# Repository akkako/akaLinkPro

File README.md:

# akaLinkPro

akaLinkPro 是一个基于 HPM5300 的高性能 CMSIS-DAP 调试器。

- 主固件：`firmware/application_5301`
- DFU/MSC Bootloader：`firmware/bootloader_dfu`
- 配置上位机（WebHID）：`docs/index.html`

构建 / 烧录 / 调试说明见 `.opencode/skills/akalinkpro-firmware/SKILL.md`。

## License

本项目采用 **Apache License 2.0** 许可，详见根目录 [`LICENSE`](LICENSE)。

```
Copyright (c) 2026 akaInstruments

Licensed under the Apache License, Version 2.0 (the "License");
you may not use this file except in compliance with the License.
You may obtain a copy of the License at

    http://www.apache.org/licenses/LICENSE-2.0
```

## 第三方组件

本项目在源码与构建中使用/参考了以下第三方组件，其版权归各自作者所有，
并按其各自的许可证分发（这些组件的原始许可证声明请见对应文件/目录）：

| 组件 | 用途 | 许可证 |
| --- | --- | --- |
| [HPMicro HPM SDK](https://github.com/hpmicro/hpm_sdk) | HPM5301 SoC/驱动/启动/链接脚本 | BSD-3-Clause |
| [ARM CMSIS-DAP](https://github.com/ARM-software/CMSIS-DAP) | CMSIS-DAP 命令引擎（`src/dap/`） | Apache-2.0 |
| [CherryUSB](https://github.com/cherry-embedded/CherryUSB) | USB 设备协议栈 | Apache-2.0 |
| [CherryRB](https://github.com/cherry-embedded/CherryRB) | 无锁环形缓冲区 | Apache-2.0 |
| [EasyFlash](https://github.com/armink/EasyFlash) | 参数持久化（`src/easyflash/`） | MIT |

> 若再分发二进制，请一并保留上述组件的版权与许可证声明。

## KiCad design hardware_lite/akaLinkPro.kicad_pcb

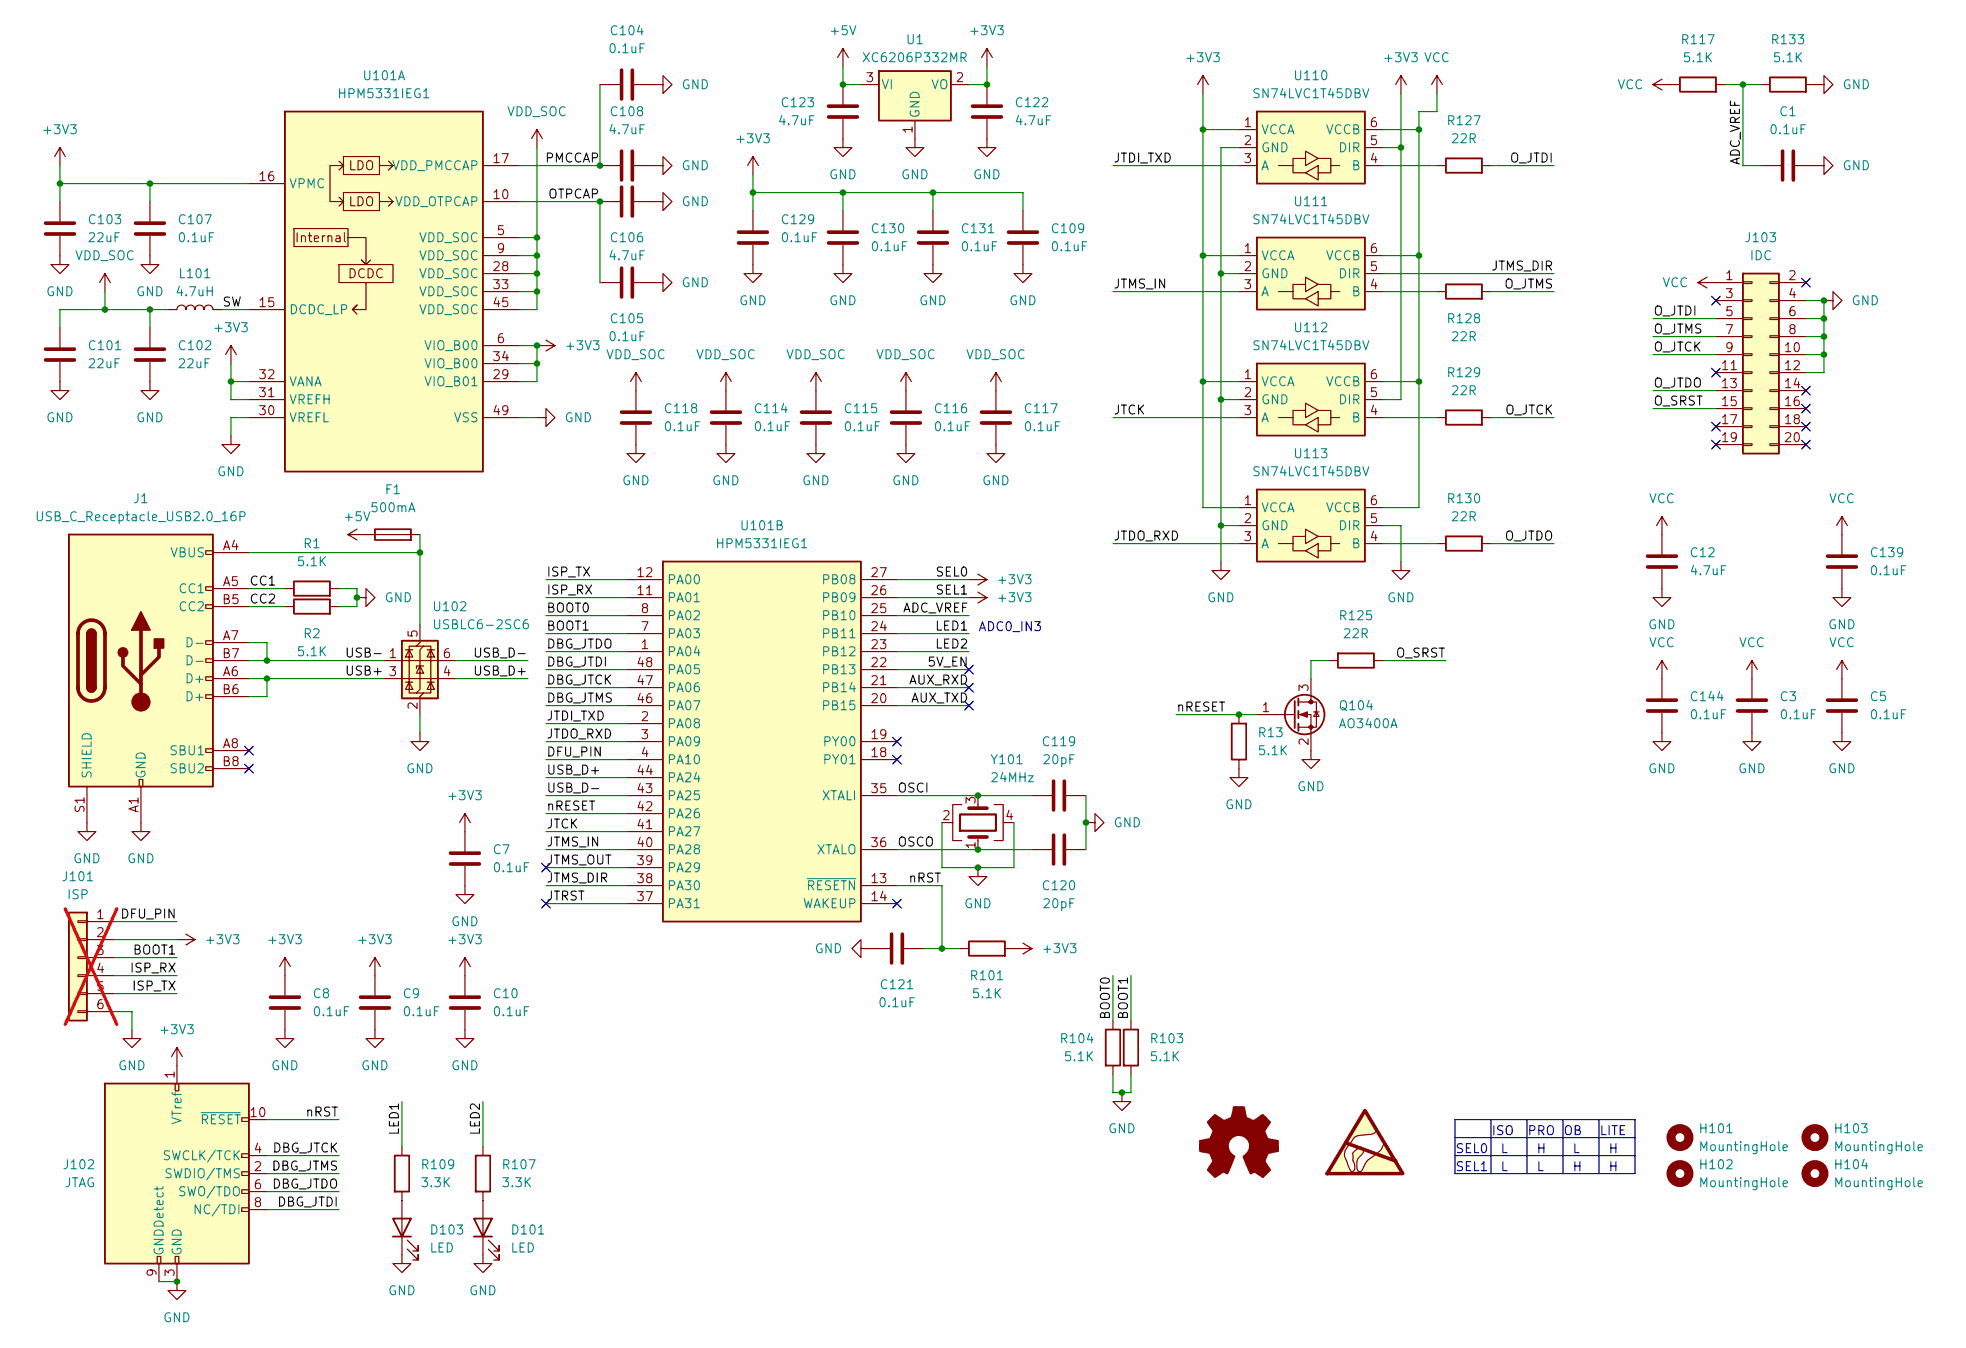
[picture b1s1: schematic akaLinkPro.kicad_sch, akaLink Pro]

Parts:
C1, C3, C5, C7, C8, C9, C10, C104, C105, C107, C109, C114, C115, C116, C117, C118, C121, C129, C130, C131, C139, C144: 0.1uF; C_0603_1608Metric
C12, C106, C108, C122, C123: 4.7uF; C_0603_1608Metric
C101, C102, C103: 22uF; C_0805_2012Metric
C119, C120: 20pF; C_0603_1608Metric
D101, D103: LED; LED_D3.0mm_Clear
F1: 500mA; Fuse_0603_1608Metric
H101, H102, H103, H104: MountingHole; MountingHole_2.5mm
J1: USB_C_Receptacle_USB2.0_16P; USB_C_Receptacle_HRO_TYPE-C-31-M-12
J101: ISP; PinHeader_1x06_P2.54mm_Vertical; not fitted
J102: JTAG; PinHeader_2x05_P1.27mm_Vertical
J103: IDC; IDC-Header_2x10_P2.54mm_Horizontal
L101: 4.7uH; L_Sunlord_SWPA3012S
Q104: AO3400A; SOT-23-3
R1, R2, R13, R101, R103, R104, R117, R133: 5.1K; R_0603_1608Metric
R107, R109: 3.3K; R_0603_1608Metric
R125, R127, R128, R129, R130: 22R; R_0603_1608Metric
U1: XC6206P332MR; SOT-23-3
U101: HPM5331IEG1; QFN-48-1EP_6x6mm_P0.4mm_EP4.2x4.2mm
U102: USBLC6-2SC6; SOT-23-6
U110, U111, U112, U113: SN74LVC1T45DBV; SOT-23-6
Y101: 24MHz; Crystal_SMD_3225-4Pin_3.2x2.5mm

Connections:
+3V3: C7.1, C8.1, C9.1, C10.1, C103.1, C107.1, C109.1, C122.1, C129.1, C130.1, C131.1, J101.2, J102.1 (VTref), R101.2, U1.2 (VO), U101.6 (VIO_B00), U101.16 (VPMC), U101.26 (PB09), U101.27 (PB08), U101.29 (VIO_B01), U101.31 (VREFH), U101.32 (VANA), U101.34 (VIO_B00), U110.1 (VCCA), U110.5 (DIR), U111.1 (VCCA), U112.1 (VCCA), U112.5 (DIR), U113.1 (VCCA)
+5V: C123.1, F1.1, U1.3 (VI)
/5V_EN: U101.22 (PB13)
/ADC_VREF: C1.1, R117.2, R133.1, U101.25 (PB10)
/AUX_RXD: U101.21 (PB14)
/AUX_TXD: U101.20 (PB15)
/BOOT0: R104.1, U101.8 (PA02)
/BOOT1: J101.3, R103.1, U101.7 (PA03)
/CC1: J1.A5 (CC1), R1.1
/CC2: J1.B5 (CC2), R2.1
/DBG_JTCK: J102.4 (SWCLK/TCK), U101.47 (PA06)
/DBG_JTDI: J102.8 (NC/TDI), U101.48 (PA05)
/DBG_JTDO: J102.6 (SWO/TDO), U101.1 (PA04)
/DBG_JTMS: J102.2 (SWDIO/TMS), U101.46 (PA07)
/DFU_PIN: J101.1, U101.4 (PA10)
/ISP_RX: J101.4, U101.11 (PA01)
/ISP_TX: J101.5, U101.12 (PA00)
/JTCK: U101.41 (PA27), U112.3 (A)
/JTDI_TXD: U101.2 (PA08), U110.3 (A)
/JTDO_RXD: U101.3 (PA09), U113.3 (A)
/JTMS_DIR: U101.38 (PA30), U111.5 (DIR)
/JTMS_IN: U101.40 (PA28), U111.3 (A)
/JTMS_OUT: U101.39 (PA29)
/JTRST: U101.37 (PA31)
/LED1: R109.1, U101.24 (PB11)
/LED2: R107.1, U101.23 (PB12)
/OSCI: C119.1, U101.35 (XTALI), Y101.3
/OSCO: C120.1, U101.36 (XTALO), Y101.1
/OTPCAP: C105.1, C106.1, U101.10 (VDD_OTPCAP)
/O_JTCK: J103.9, R129.2
/O_JTDI: J103.5, R127.2
/O_JTDO: J103.13, R130.2
/O_JTMS: J103.7, R128.2
/O_SRST: J103.15, R125.1
/PMCCAP: C104.1, C108.1, U101.17 (VDD_PMCCAP)
/SW: L101.2, U101.15 (DCDC_LP)
/USB+: J1.A6 (D+), J1.B6 (D+), U102.3 (I/O2)
/USB-: J1.A7 (D-), J1.B7 (D-), U102.1 (I/O1)
/USB_D+: U101.44 (PA24), U102.4 (I/O2)
/USB_D-: U101.43 (PA25), U102.6 (I/O1)
/nRESET: Q104.1 (G), R13.2, U101.42 (PA26)
/nRST: C121.1, J102.10 (~RESET), R101.1, U101.13 (~RESETN)
GND: C1.2, C3.2, C5.2, C7.2, C8.2, C9.2, C10.2, C12.2, C101.2, C102.2, C103.2, C104.2, C105.2, C106.2, C107.2, C108.2, C109.2, C114.2, C115.2, C116.2, C117.2, C118.2, C119.2, C120.2, C121.2, C122.2, C123.2, C129.2, C130.2, C131.2, C139.2, C144.2, D101.1 (K), D103.1 (K), J1.A1 (GND), J1.A12 (GND), J1.B1 (GND), J1.B12 (GND), J1.S1 (SHIELD), J101.6, J102.3 (GND), J102.5 (GND), J102.9 (GNDDetect), J103.4, J103.6, J103.8, J103.10, J103.12, Q104.2 (S), R1.2, R2.2, R13.1, R103.2, R104.2, R133.2, U1.1 (GND), U101.30 (VREFL), U101.49 (VSS), U102.2 (GND), U110.2 (GND), U111.2 (GND), U112.2 (GND), U113.2 (GND), U113.5 (DIR), Y101.2, Y101.4
unnamed: D101.2 (A), R107.2
unnamed: D103.2 (A), R109.2
unnamed: Q104.3 (D), R125.2
unnamed: F1.2, J1.A4 (VBUS), J1.A9 (VBUS), J1.B4 (VBUS), J1.B9 (VBUS), U102.5 (VBUS)
unnamed: R127.1, U110.4 (B)
unnamed: R128.1, U111.4 (B)
unnamed: R129.1, U112.4 (B)
unnamed: R130.1, U113.4 (B)
VCC: C3.1, C5.1, C12.1, C139.1, C144.1, J103.1, R117.1, U110.6 (VCCB), U111.6 (VCCB), U112.6 (VCCB), U113.6 (VCCB)
VDD_SOC: C101.1, C102.1, C114.1, C115.1, C116.1, C117.1, C118.1, L101.1, U101.5 (VDD_SOC), U101.9 (VDD_SOC), U101.28 (VDD_SOC), U101.33 (VDD_SOC), U101.45 (VDD_SOC)

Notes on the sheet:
ISO
ADC0_IN3
PRO
SEL1
SEL0
LITE

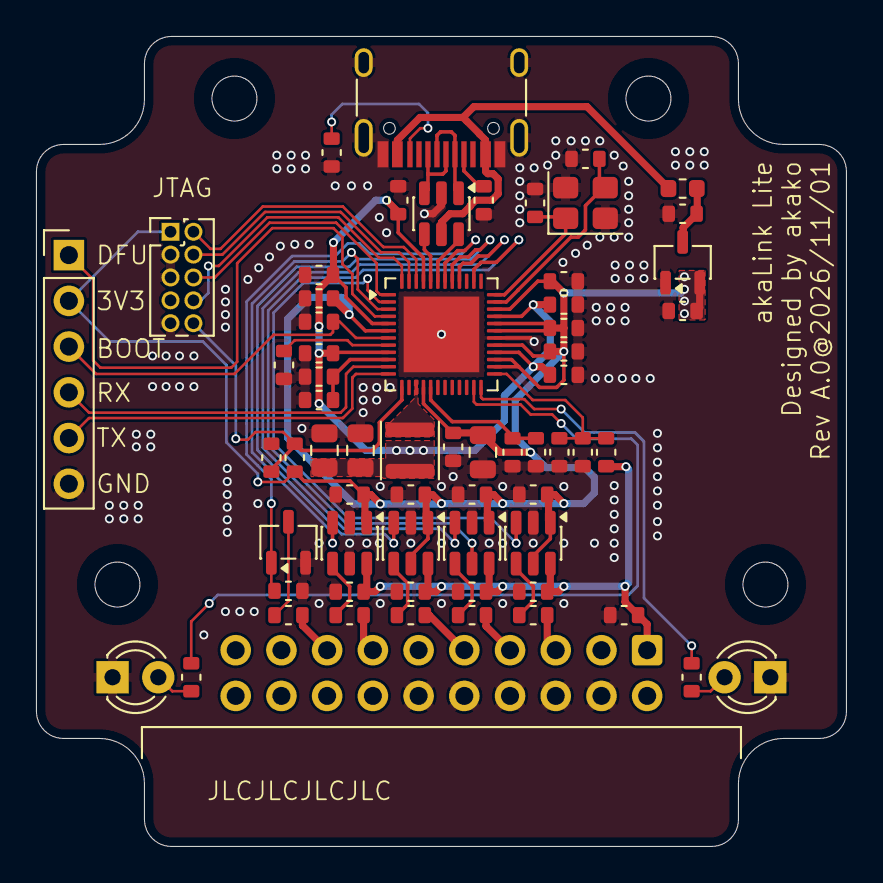
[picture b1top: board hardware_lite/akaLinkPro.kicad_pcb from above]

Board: 2 copper layers, 45.0 x 45.0 mm, 68 parts (0 on the bottom side), 48 nets.

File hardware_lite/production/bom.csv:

Designator,Footprint,Quantity,Value,LCSC Part #
"C1, C10, C104, C105, C107, C109, C114, C115, C116, C117, C118, C121, C129, C130, C131, C139, C144, C3, C5, C7, C8, C9",0603,22,0.1uF,
"C101, C102, C103",0805,3,22uF,
"C106, C108, C12, C122, C123",0603,5,4.7uF,
"C119, C120",0603,2,20pF,
"D101, D103",LED_D3.0mm_Clear,2,LED,
F1,0603,1,500mA,
J1,USB_C_Receptacle_HRO_TYPE-C-31-M-12,1,USB_C_Receptacle_USB2.0_16P,
J102,PinHeader_2x05_P1.27mm_Vertical,1,JTAG,
J103,IDC-Header_2x10_P2.54mm_Horizontal,1,IDC,
L101,L_Sunlord_SWPA3012S,1,4.7uH,
Q104,SOT-23-3,1,AO3400A,
"R1, R101, R103, R104, R117, R13, R133, R2",0603,8,5.1K,
"R107, R109",0603,2,3.3K,
"R125, R127, R128, R129, R130",0603,5,22R,
U1,SOT-23-3,1,XC6206P332MR,
U101,QFN-48-1EP_6x6mm_P0.4mm_EP4.2x4.2mm,1,HPM5331IEG1,
U102,SOT-23-6,1,USBLC6-2SC6,
"U110, U111, U112, U113",SOT-23-6,4,SN74LVC1T45DBV,
Y101,Crystal_SMD_3225-4Pin_3.2x2.5mm,1,24MHz,

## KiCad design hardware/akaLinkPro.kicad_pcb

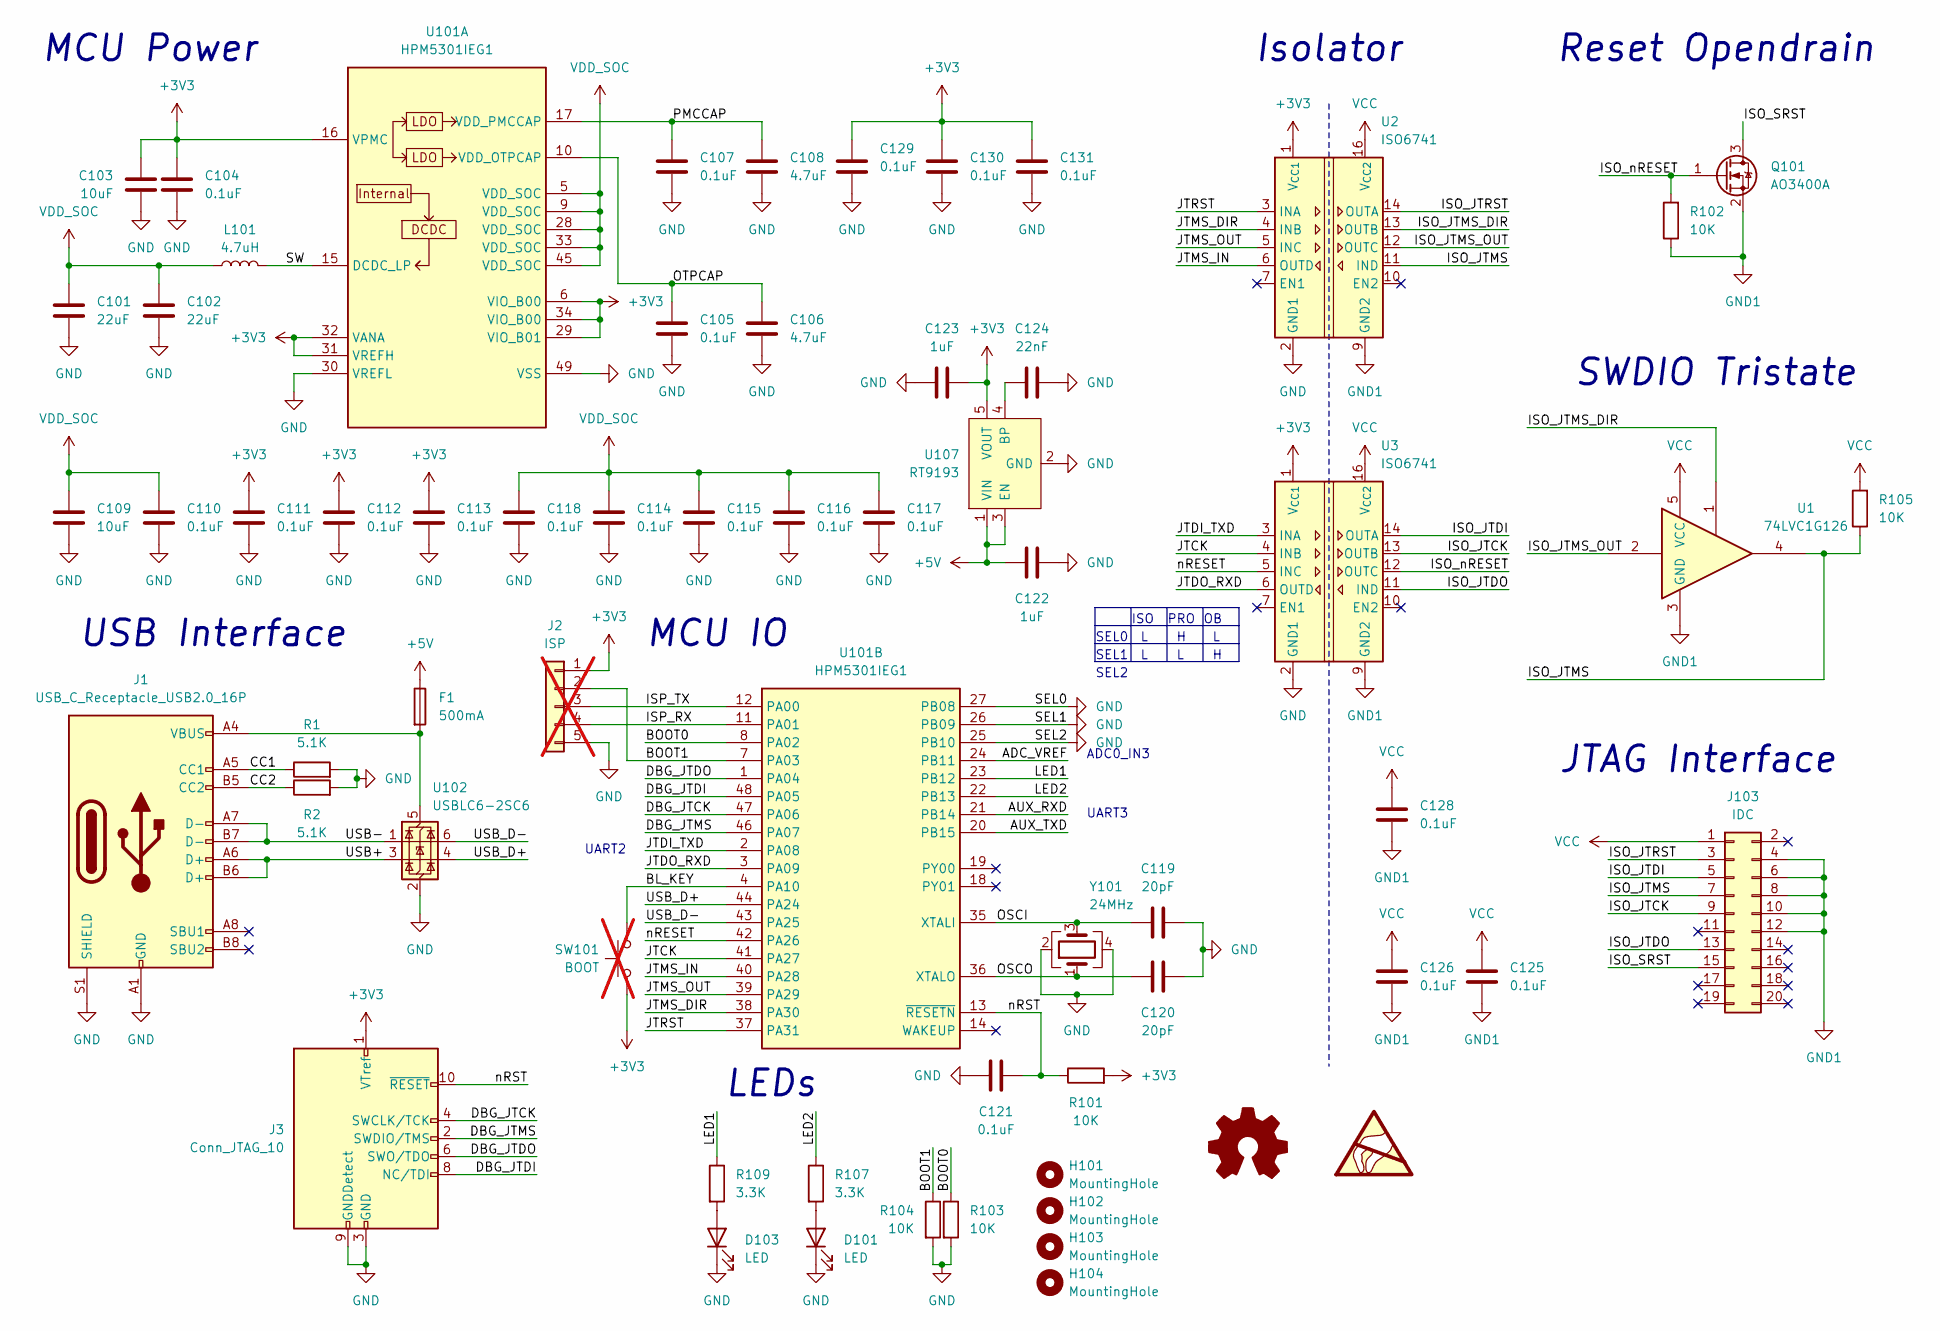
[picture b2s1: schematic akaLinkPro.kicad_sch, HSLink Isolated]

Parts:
C101, C102: 22uF; C_0805_2012Metric
C103, C109: 10uF; C_0805_2012Metric
C104, C105, C107, C110, C111, C112, C113, C114, C115, C116, C117, C118, C121, C125, C126, C128, C129, C130, C131: 0.1uF; C_0603_1608Metric
C106, C108: 4.7uF; C_0603_1608Metric
C119, C120: 20pF; C_0603_1608Metric
C122, C123: 1uF; C_0603_1608Metric
C124: 22nF; C_0603_1608Metric
D101, D103: LED; LED_0603_1608Metric
F1: 500mA; Fuse_0805_2012Metric
H101, H102, H103, H104: MountingHole; MountingHole_2.5mm
J1: USB_C_Receptacle_USB2.0_16P; USB_C_Receptacle_HRO_TYPE-C-31-M-12
J2: ISP; PinHeader_1x05_P2.54mm_Vertical; not fitted
J3: Conn_JTAG_10; PinHeader_2x05_P1.27mm_Vertical
J103: IDC; IDC-Header_2x10_P2.54mm_Horizontal
L101: 4.7uH; L_Sunlord_SWPA252012S
Q101: AO3400A; SOT-23
R1, R2: 5.1K; R_0603_1608Metric
R101, R102, R103, R104, R105: 10K; R_0603_1608Metric
R107, R109: 3.3K; R_0603_1608Metric
SW101: BOOT; PinHeader_1x02_P2.54mm_Vertical; not fitted
U1: 74LVC1G126; SOT-23-5
U2, U3: ISO6741; SOIC-16W_7.5x10.3mm_P1.27mm
U101: HPM5301IEG1; QFN-48-1EP_6x6mm_P0.4mm_EP4.2x4.2mm
U102: USBLC6-2SC6; SOT-23-6
U107: RT9193; SOT-23-5
Y101: 24MHz; Crystal_SMD_3225-4Pin_3.2x2.5mm

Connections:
+3V3: C103.1, C104.1, C111.1, C112.1, C113.1, C123.1, C129.1, C130.1, C131.1, J2.1, J3.1 (VTref), R101.2, SW101.2, U2.1 (V_{CC1}), U3.1 (V_{CC1}), U101.6 (VIO_B00), U101.16 (VPMC), U101.29 (VIO_B01), U101.31 (VREFH), U101.32 (VANA), U101.34 (VIO_B00), U107.5 (VOUT)
+5V: C122.1, F1.1, U107.1 (VIN), U107.3 (EN)
/ADC_VREF: U101.24 (PB11)
/AUX_RXD: U101.21 (PB14)
/AUX_TXD: U101.20 (PB15)
/BL_KEY: SW101.1, U101.4 (PA10)
/BOOT0: R103.1, U101.8 (PA02)
/BOOT1: J2.2, R104.1, U101.7 (PA03)
/CC1: J1.A5 (CC1), R1.1
/CC2: J1.B5 (CC2), R2.1
/DBG_JTCK: J3.4 (SWCLK/TCK), U101.47 (PA06)
/DBG_JTDI: J3.8 (NC/TDI), U101.48 (PA05)
/DBG_JTDO: J3.6 (SWO/TDO), U101.1 (PA04)
/DBG_JTMS: J3.2 (SWDIO/TMS), U101.46 (PA07)
/ISO_JTCK: J103.9, U3.13 (OUTB)
/ISO_JTDI: J103.5, U3.14 (OUTA)
/ISO_JTDO: J103.13, U3.11 (IND)
/ISO_JTMS: J103.7, R105.1, U1.4, U2.11 (IND)
/ISO_JTMS_DIR: U1.1, U2.13 (OUTB)
/ISO_JTMS_OUT: U1.2, U2.12 (OUTC)
/ISO_JTRST: J103.3, U2.14 (OUTA)
/ISO_SRST: J103.15, Q101.3 (D)
/ISO_nRESET: Q101.1 (G), R102.2, U3.12 (OUTC)
/ISP_RX: J2.4, U101.11 (PA01)
/ISP_TX: J2.3, U101.12 (PA00)
/JTCK: U3.4 (INB), U101.41 (PA27)
/JTDI_TXD: U3.3 (INA), U101.2 (PA08)
/JTDO_RXD: U3.6 (OUTD), U101.3 (PA09)
/JTMS_DIR: U2.4 (INB), U101.38 (PA30)
/JTMS_IN: U2.6 (OUTD), U101.40 (PA28)
/JTMS_OUT: U2.5 (INC), U101.39 (PA29)
/JTRST: U2.3 (INA), U101.37 (PA31)
/LED1: R109.1, U101.23 (PB12)
/LED2: R107.1, U101.22 (PB13)
/OSCI: C119.1, U101.35 (XTALI), Y101.3
/OSCO: C120.1, U101.36 (XTALO), Y101.1
/OTPCAP: C105.1, C106.1, U101.10 (VDD_OTPCAP)
/PMCCAP: C107.1, C108.1, U101.17 (VDD_PMCCAP)
/SW: L101.2, U101.15 (DCDC_LP)
/USB+: J1.A6 (D+), J1.B6 (D+), U102.3 (I/O2)
/USB-: J1.A7 (D-), J1.B7 (D-), U102.1 (I/O1)
/USB_D+: U101.44 (PA24), U102.4 (I/O2)
/USB_D-: U101.43 (PA25), U102.6 (I/O1)
/nRESET: U3.5 (INC), U101.42 (PA26)
/nRST: C121.1, J3.10 (~RESET), R101.1, U101.13 (~RESETN)
GND: C101.2, C102.2, C103.2, C104.2, C105.2, C106.2, C107.2, C108.2, C109.2, C110.2, C111.2, C112.2, C113.2, C114.2, C115.2, C116.2, C117.2, C118.2, C119.2, C120.2, C121.2, C122.2, C123.2, C124.2, C129.2, C130.2, C131.2, D101.1 (K), D103.1 (K), J1.A1 (GND), J1.A12 (GND), J1.B1 (GND), J1.B12 (GND), J1.S1 (SHIELD), J2.5, J3.3 (GND), J3.5 (GND), J3.9 (GNDDetect), R1.2, R2.2, R103.2, R104.2, U2.2 (GND1), U2.8 (GND1), U3.2 (GND1), U3.8 (GND1), U101.25 (PB10), U101.26 (PB09), U101.27 (PB08), U101.30 (VREFL), U101.49 (VSS), U102.2 (GND), U107.2 (GND), Y101.2, Y101.4
GND1: C125.2, C126.2, C128.2, J103.4, J103.6, J103.8, J103.10, J103.12, Q101.2 (S), R102.1, U1.3 (GND), U2.9 (GND2), U2.15 (GND2), U3.9 (GND2), U3.15 (GND2)
unnamed: D101.2 (A), R107.2
unnamed: D103.2 (A), R109.2
unnamed: F1.2, J1.A4 (VBUS), J1.A9 (VBUS), J1.B4 (VBUS), J1.B9 (VBUS), U102.5 (VBUS)
unnamed: C124.1, U107.4 (BP)
VCC: C125.1, C126.1, C128.1, J103.1, R105.2, U1.5 (VCC), U2.16 (V_{CC2}), U3.16 (V_{CC2})
VDD_SOC: C101.1, C102.1, C109.1, C110.1, C114.1, C115.1, C116.1, C117.1, C118.1, L101.1, U101.5 (VDD_SOC), U101.9 (VDD_SOC), U101.28 (VDD_SOC), U101.33 (VDD_SOC), U101.45 (VDD_SOC)

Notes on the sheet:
ISO
ADC0_IN3
PRO
JTAG Interface
UART2
Isolator
USB Interface
SEL1
SEL0
Reset Opendrain
MCU Power
UART3
MCU IO
SWDIO Tristate
LEDs
SEL2

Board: 2 copper layers, 60 parts (0 on the bottom side), 50 nets, no tracks yet.

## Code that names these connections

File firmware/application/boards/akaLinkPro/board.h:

/*
 * Copyright (c) 2023-2026 HPMicro
 *
 * SPDX-License-Identifier: BSD-3-Clause
 *
 */

#ifndef _HPM_BOARD_H
#define _HPM_BOARD_H
#include <stdio.h>
#include <stdarg.h>
#include "hpm_common.h"
#include "hpm_clock_drv.h"
#include "hpm_soc.h"
#include "hpm_soc_feature.h"
#include "pinmux.h"
#if !defined(CONFIG_NDEBUG_CONSOLE) || !CONFIG_NDEBUG_CONSOLE
#include "hpm_debug_console.h"
#endif

#define BOARD_NAME "akaLinkPro"
#define BOARD_UF2_SIGNATURE (0x0A4D5048UL)
#define BOARD_DFU_SIGNATURE (0x48504D21UL)
#define BOARD_BGPR HPM_BGPR0

/* core section */
#ifndef BOARD_RUNNING_CORE
#define BOARD_RUNNING_CORE HPM_CORE0
#endif

/* uart section */
#ifndef BOARD_APP_UART_BASE
#define BOARD_APP_UART_BASE HPM_UART3
#define BOARD_APP_UART_IRQ IRQn_UART3
#define BOARD_APP_UART_BAUDRATE (115200UL)
#define BOARD_APP_UART_CLK_NAME clock_uart3
#define BOARD_APP_UART_RX_DMA_REQ HPM_DMA_SRC_UART3_RX
#define BOARD_APP_UART_TX_DMA_REQ HPM_DMA_SRC_UART3_TX
#endif

#define BOARD_APP_UART_BREAK_SIGNAL_PIN IOC_PAD_PA26

#if !defined(CONFIG_NDEBUG_CONSOLE) || !CONFIG_NDEBUG_CONSOLE
#ifndef BOARD_CONSOLE_TYPE
#define BOARD_CONSOLE_TYPE CONSOLE_TYPE_UART
#endif

#if BOARD_CONSOLE_TYPE == CONSOLE_TYPE_UART
#ifndef BOARD_CONSOLE_UART_BASE
#define BOARD_CONSOLE_UART_BASE HPM_UART0
#define BOARD_CONSOLE_UART_CLK_NAME clock_uart0
#define BOARD_CONSOLE_UART_IRQ IRQn_UART0
#define BOARD_CONSOLE_UART_TX_DMA_REQ HPM_DMA_SRC_UART0_TX
#define BOARD_CONSOLE_UART_RX_DMA_REQ HPM_DMA_SRC_UART0_RX
#endif
#define BOARD_CONSOLE_UART_BAUDRATE (115200UL)
#endif
#endif

/* nor flash section */
#define BOARD_FLASH_BASE_ADDRESS (0x80000000UL) /* Check */
#define BOARD_FLASH_SIZE (SIZE_1MB)

/* gpiom section */
#define BOARD_APP_GPIOM_BASE HPM_GPIOM
#define BOARD_APP_GPIOM_USING_CTRL HPM_FGPIO
#define BOARD_APP_GPIOM_USING_CTRL_NAME gpiom_core0_fast

/* User button */
#define BOARD_APP_GPIO_CTRL HPM_GPIO0
#define BOARD_APP_GPIO_INDEX GPIO_DI_GPIOA
#define BOARD_APP_GPIO_PIN 3
#define BOARD_APP_GPIO_IRQ IRQn_GPIO0_A
#define BOARD_BUTTON_PRESSED_VALUE 1

#ifndef BOARD_SHOW_CLOCK
#define BOARD_SHOW_CLOCK 1
#endif
#ifndef BOARD_SHOW_BANNER
#define BOARD_SHOW_BANNER 1
#endif

/*
    Pin connection:

    UART_RTS    PA05            init as low     GPIO0
    UART_DTR    PA06            init as low     GPIO0
    WS2812      PA07 (SPI0)
    UART_TXD    PA08 (USART3)   init as low     GPIO0
    UART_RXD    PA09 (USART3)   init as input   GPIO0
    JTCK        PA27            init as high    FGPIO
    JTMS_IN     PA28            init as input   FGPIO
    JTMS_OUT    PA29            init as high    FGPIO
    JTMS_DIR    PA30            init as high    FGPIO
    JTDO        PB12            init as input   FGPIO
    JTDI        PB13            init as high    FGPIO
    JTRST       PB14            init as high    FGPIO
    nRESET      PB15            init as low     GPIO0

    Unused Pin:

    PA04 (PORT_EN NC)       init as low         GPIO0
    PA10 (PWMDAC NC)        init as low         GPIO0
    PA26 (SPI_CS)           init as low         GPIO0
    PA31 (P_EN NC)          init as low         GPIO0
    PB08 (ADC_VREF NC)      init as low         GPIO0
    PB09 (ADC_TVCC NC)      init as low         GPIO0
    PB10 (SPI_CS)           init as low         GPIO0
    PB11 (JTCK)             init as float       GPIO0
*/

#define BOARD_PIN_UART_TXD      IOC_PAD_PA08
#define BOARD_PIN_UART_RXD      IOC_PAD_PA09
#define BOARD_PIN_UART_RTS      IOC_PAD_PA05
#define BOARD_PIN_UART_DTR      IOC_PAD_PA06

#define BOARD_PIN_JTCK          IOC_PAD_PA27
#define BOARD_PIN_JTMS_IN       IOC_PAD_PA28
#define BOARD_PIN_JTMS_OUT      IOC_PAD_PA29
#define BOARD_PIN_JTMS_DIR      IOC_PAD_PA30
#define BOARD_PIN_JTDO          IOC_PAD_PB12
#define BOARD_PIN_JTDI          IOC_PAD_PB13
#define BOARD_PIN_JTRST         IOC_PAD_PB14
#define BOARD_PIN_nRESET        IOC_PAD_PB15

#define BOARD_PIN_UNUSED_PORTEN IOC_PAD_PA04
#define BOARD_PIN_UNUSED_PWM    IOC_PAD_PA10
#define BOARD_PIN_UNUSED_CS1    IOC_PAD_PA26
#define BOARD_PIN_UNUSED_CS2    IOC_PAD_PB10
#define BOARD_PIN_UNUSED_PEN    IOC_PAD_PA31
#define BOARD_PIN_UNUSED_VREF   IOC_PAD_PB08
#define BOARD_PIN_UNUSED_TVCC   IOC_PAD_PB09
#define BOARD_PIN_UNUSED_JTCK   IOC_PAD_PB11

#define PIN_GPIOM_BASE    HPM_GPIOM
#define PIN_GPIO          HPM_FGPIO
#define PIN_GPIOM         gpiom_core0_fast


#if defined(__cplusplus)
extern "C"
{
#endif /* __cplusplus */

    typedef void (*board_timer_cb)(void);

    void board_init_gpio_pins(void);
    void board_init_usb(USB_Type *ptr);
    void board_init_console(void);
    void board_init_uart(UART_Type *ptr);

    void board_init(void);
    void board_init_usb_dp_dm_pins(void);
    void board_init_clock(void);
    void board_delay_us(uint32_t us);
    void board_delay_ms(uint32_t ms);
    void board_ungate_mchtmr_at_lp_mode(void);

    void board_init_pmp(void);
    uint32_t board_init_uart_clock(UART_Type *ptr);
    void init_uart_pins(UART_Type *ptr);
    void init_uart_pin_as_gpio(UART_Type *ptr);
    void init_usb_pins(USB_Type *ptr);
#if defined(__cplusplus)
}
#endif /* __cplusplus */
#endif /* _HPM_BOARD_H */

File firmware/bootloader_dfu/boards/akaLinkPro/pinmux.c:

/*
 * Copyright (c) 2023 HPMicro
 *
 * SPDX-License-Identifier: BSD-3-Clause
 *
 */

/*
 * Note:
 *  PY and PZ IOs: if any SOC pin function needs to be routed to these IOs,
 *  besides of IOC, PIOC/BIOC needs to be configured SOC_GPIO_X_xx, so that
 *  expected SoC function can be enabled on these IOs.
 *
 */
#include "board.h"
#include "pinmux.h"
#include "hpm_gpio_drv.h"
#include "hpm_gpiom_drv.h"

// Miscellaneous
#define DFU_PIN IOC_PAD_PA10
#define LED1_PIN IOC_PAD_PB11
#define LED2_PIN IOC_PAD_PB12
#define SEL0_PIN IOC_PAD_PB08
#define SEL1_PIN IOC_PAD_PB09

// power
#define BUS5V_EN_PIN IOC_PAD_PB13
#define ADC_VREF_PIN IOC_PAD_PB10

// UART0
#define ISP_TX_PIN IOC_PAD_PA00
#define ISP_RX_PIN IOC_PAD_PA01

// UART3
#define AUX_RX_PIN IOC_PAD_PB14
#define AUX_TX_PIN IOC_PAD_PB15

// UART2/SWJ
#define JTDI_TXD_PIN IOC_PAD_PA08
#define JTDO_RXD_PIN IOC_PAD_PA09

// SWJ
#define JTCK_PIN IOC_PAD_PA27
#define JTMS_IN_PIN IOC_PAD_PA28
#define JTMS_OUT_PIN IOC_PAD_PA29
#define JTMS_DIR_PIN IOC_PAD_PA30
#define JTRST_PIN IOC_PAD_PA31
#define nRESET_PIN IOC_PAD_PA26

// USB
#define USB_DP_PIN IOC_PAD_PA24
#define USB_DN_PIN IOC_PAD_PA25

void init_py_pins_as_pgpio(void)
{
    /* Set PY00-PY05 default function to PGPIO */
    HPM_PIOC->PAD[IOC_PAD_PY00].FUNC_CTL = PIOC_PY00_FUNC_CTL_PGPIO_Y_00;
    HPM_PIOC->PAD[IOC_PAD_PY01].FUNC_CTL = PIOC_PY01_FUNC_CTL_PGPIO_Y_01;
    HPM_PIOC->PAD[IOC_PAD_PY02].FUNC_CTL = PIOC_PY02_FUNC_CTL_PGPIO_Y_02;
    HPM_PIOC->PAD[IOC_PAD_PY03].FUNC_CTL = PIOC_PY03_FUNC_CTL_PGPIO_Y_03;
    HPM_PIOC->PAD[IOC_PAD_PY04].FUNC_CTL = PIOC_PY04_FUNC_CTL_PGPIO_Y_04;
    HPM_PIOC->PAD[IOC_PAD_PY05].FUNC_CTL = PIOC_PY05_FUNC_CTL_PGPIO_Y_05;
}

void init_gpio_swj_pins(void)
{
    // set alternate function as gpio
    HPM_IOC->PAD[JTDI_TXD_PIN].FUNC_CTL = IOC_PAD_FUNC_CTL_ALT_SELECT_SET(0);
    HPM_IOC->PAD[JTDO_RXD_PIN].FUNC_CTL = IOC_PAD_FUNC_CTL_ALT_SELECT_SET(0);
    HPM_IOC->PAD[JTCK_PIN].FUNC_CTL = IOC_PAD_FUNC_CTL_ALT_SELECT_SET(0);
    HPM_IOC->PAD[JTMS_IN_PIN].FUNC_CTL = IOC_PAD_FUNC_CTL_ALT_SELECT_SET(0);
    HPM_IOC->PAD[JTMS_OUT_PIN].FUNC_CTL = IOC_PAD_FUNC_CTL_ALT_SELECT_SET(0);
    HPM_IOC->PAD[JTMS_DIR_PIN].FUNC_CTL = IOC_PAD_FUNC_CTL_ALT_SELECT_SET(0);
    HPM_IOC->PAD[JTRST_PIN].FUNC_CTL = IOC_PAD_FUNC_CTL_ALT_SELECT_SET(0);
    HPM_IOC->PAD[nRESET_PIN].FUNC_CTL = IOC_PAD_FUNC_CTL_ALT_SELECT_SET(0);

    // set pad parameter
    HPM_IOC->PAD[JTDI_TXD_PIN].PAD_CTL = IOC_PAD_PAD_CTL_SR_SET(1) |
                                         IOC_PAD_PAD_CTL_SPD_SET(3);

    // set pin controller
    gpiom_set_pin_controller(HPM_GPIOM, GPIO_GET_PORT_INDEX(JTDI_TXD_PIN), GPIO_GET_PIN_INDEX(JTDI_TXD_PIN), gpiom_soc_gpio0);

    // set output/input mode
    gpio_set_pin_output(HPM_FGPIO, GPIO_GET_PORT_INDEX(JTDI_TXD_PIN), GPIO_GET_PIN_INDEX(JTDI_TXD_PIN));

    // set pin default state
    gpio_write_pin(HPM_FGPIO, GPIO_GET_PORT_INDEX(JTDI_TXD_PIN), GPIO_GET_PIN_INDEX(JTDI_TXD_PIN), 1);
}

/**
 * @brief Init UART pins
 * @param ptr UART_Type instance
 */
void init_uart_pins(UART_Type *ptr)
{
    if (ptr == HPM_UART0)
    {
        HPM_IOC->PAD[ISP_TX_PIN].FUNC_CTL = IOC_PA00_FUNC_CTL_UART0_TXD;
        HPM_IOC->PAD[ISP_RX_PIN].FUNC_CTL = IOC_PA01_FUNC_CTL_UART0_RXD;
    }
    else if (ptr == HPM_UART2)
    {
        HPM_IOC->PAD[JTDI_TXD_PIN].FUNC_CTL = IOC_PA08_FUNC_CTL_UART2_TXD;
        HPM_IOC->PAD[JTDO_RXD_PIN].FUNC_CTL = IOC_PA09_FUNC_CTL_UART2_RXD;
    }
    else if (ptr == HPM_UART3)
    {
        HPM_IOC->PAD[AUX_TX_PIN].FUNC_CTL = IOC_PB15_FUNC_CTL_UART3_TXD;
        HPM_IOC->PAD[AUX_RX_PIN].FUNC_CTL = IOC_PB14_FUNC_CTL_UART3_RXD;
    }
    else
    {
        ;
    }
}

/**
 * @brief Init LED pins
 * @param None
 */
void init_led_pins(void)
{
    uint32_t pad_ctl_slow = IOC_PAD_PAD_CTL_HYS_SET(0) |
                            IOC_PAD_PAD_CTL_PRS_SET(0) |
                            IOC_PAD_PAD_CTL_PS_SET(0) |
                            IOC_PAD_PAD_CTL_PE_SET(0) |
                            IOC_PAD_PAD_CTL_KE_SET(0) |
                            IOC_PAD_PAD_CTL_OD_SET(0) |
                            IOC_PAD_PAD_CTL_SR_SET(0) |
                            IOC_PAD_PAD_CTL_SPD_SET(0) |
                            IOC_PAD_PAD_CTL_DS_SET(0);

    // set alternate function as gpio
    HPM_IOC->PAD[LED1_PIN].FUNC_CTL = IOC_PAD_FUNC_CTL_ALT_SELECT_SET(0);
    HPM_IOC->PAD[LED2_PIN].FUNC_CTL = IOC_PAD_FUNC_CTL_ALT_SELECT_SET(0);

    // set pad parameter
    HPM_IOC->PAD[LED1_PIN].PAD_CTL = pad_ctl_slow;
    HPM_IOC->PAD[LED2_PIN].PAD_CTL = pad_ctl_slow;

    // set pin controller
    gpiom_set_pin_controller(HPM_GPIOM, GPIO_GET_PORT_INDEX(LED1_PIN), GPIO_GET_PIN_INDEX(LED1_PIN), gpiom_soc_gpio0);
    gpiom_set_pin_controller(HPM_GPIOM, GPIO_GET_PORT_INDEX(LED2_PIN), GPIO_GET_PIN_INDEX(LED2_PIN), gpiom_soc_gpio0);

    // set output/input mode
    gpio_set_pin_output(HPM_GPIO0, GPIO_GET_PORT_INDEX(LED1_PIN), GPIO_GET_PIN_INDEX(LED1_PIN));
    gpio_set_pin_output(HPM_GPIO0, GPIO_GET_PORT_INDEX(LED2_PIN), GPIO_GET_PIN_INDEX(LED2_PIN));

    // set pin default state
    gpio_write_pin(HPM_GPIO0, GPIO_GET_PORT_INDEX(LED1_PIN), GPIO_GET_PIN_INDEX(LED1_PIN), 0);
    gpio_write_pin(HPM_GPIO0, GPIO_GET_PORT_INDEX(LED2_PIN), GPIO_GET_PIN_INDEX(LED2_PIN), 0);
}

/**
 * @brief Init power control and sense pin
 * @param None
 */
void init_power_pins(void)
{
    // set alternate function as gpio
    HPM_IOC->PAD[BUS5V_EN_PIN].FUNC_CTL = IOC_PAD_FUNC_CTL_ALT_SELECT_SET(0);

    // set pad parameter
    HPM_IOC->PAD[BUS5V_EN_PIN].PAD_CTL = IOC_PAD_PAD_CTL_HYS_SET(0) |
                                         IOC_PAD_PAD_CTL_PRS_SET(0) |
                                         IOC_PAD_PAD_CTL_PS_SET(0) |
                                         IOC_PAD_PAD_CTL_PE_SET(0) |
                                         IOC_PAD_PAD_CTL_KE_SET(0) |
                                         IOC_PAD_PAD_CTL_OD_SET(0) |
                                         IOC_PAD_PAD_CTL_SR_SET(0) |
                                         IOC_PAD_PAD_CTL_SPD_SET(0) |
                                         IOC_PAD_PAD_CTL_DS_SET(0);

    // set pin controller
    gpiom_set_pin_controller(HPM_GPIOM, GPIO_GET_PORT_INDEX(BUS5V_EN_PIN), GPIO_GET_PIN_INDEX(BUS5V_EN_PIN), gpiom_soc_gpio0);

    // set output/input mode
    gpio_set_pin_output(HPM_GPIO0, GPIO_GET_PORT_INDEX(BUS5V_EN_PIN), GPIO_GET_PIN_INDEX(BUS5V_EN_PIN));

    // set pin default state
    gpio_write_pin(HPM_GPIO0, GPIO_GET_PORT_INDEX(BUS5V_EN_PIN), GPIO_GET_PIN_INDEX(BUS5V_EN_PIN), 0);

    // set alternate function as analog
    HPM_IOC->PAD[BUS5V_EN_PIN].FUNC_CTL = IOC_PAD_FUNC_CTL_ANALOG_MASK;
}

void init_model_sel_pins(void)
{
}

void init_dfu_pins(void)
{
    uint32_t pad_ctl = IOC_PAD_PAD_CTL_HYS_SET(1) | // hyster enable
                       IOC_PAD_PAD_CTL_PRS_SET(0) | // pull res 100k
                       IOC_PAD_PAD_CTL_PS_SET(0) |  // pull down
                       IOC_PAD_PAD_CTL_PE_SET(1) |  // pull enable
                       IOC_PAD_PAD_CTL_KE_SET(0) |
                       IOC_PAD_PAD_CTL_OD_SET(0) |
                       IOC_PAD_PAD_CTL_SR_SET(0) |
                       IOC_PAD_PAD_CTL_SPD_SET(0) |
                       IOC_PAD_PAD_CTL_DS_SET(0);

    HPM_IOC->PAD[DFU_PIN].FUNC_CTL = IOC_PAD_FUNC_CTL_ALT_SELECT_SET(0);
    HPM_IOC->PAD[DFU_PIN].PAD_CTL = pad_ctl;

    gpiom_set_pin_controller(HPM_GPIOM, GPIO_GET_PORT_INDEX(DFU_PIN), GPIO_GET_PIN_INDEX(DFU_PIN), gpiom_soc_gpio0);
    gpio_set_pin_input(HPM_GPIO0, GPIO_GET_PORT_INDEX(DFU_PIN), GPIO_GET_PIN_INDEX(DFU_PIN));
}

void init_usb_pins(USB_Type *ptr)
{
    if (ptr == HPM_USB0)
    {
        HPM_IOC->PAD[USB_DP_PIN].FUNC_CTL = IOC_PAD_FUNC_CTL_ANALOG_MASK;
        HPM_IOC->PAD[USB_DN_PIN].FUNC_CTL = IOC_PAD_FUNC_CTL_ANALOG_MASK;
    }
}
